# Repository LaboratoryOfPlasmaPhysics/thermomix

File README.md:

View this project on [CADLAB.io](https://cadlab.io/project/27332). 

# thermomix

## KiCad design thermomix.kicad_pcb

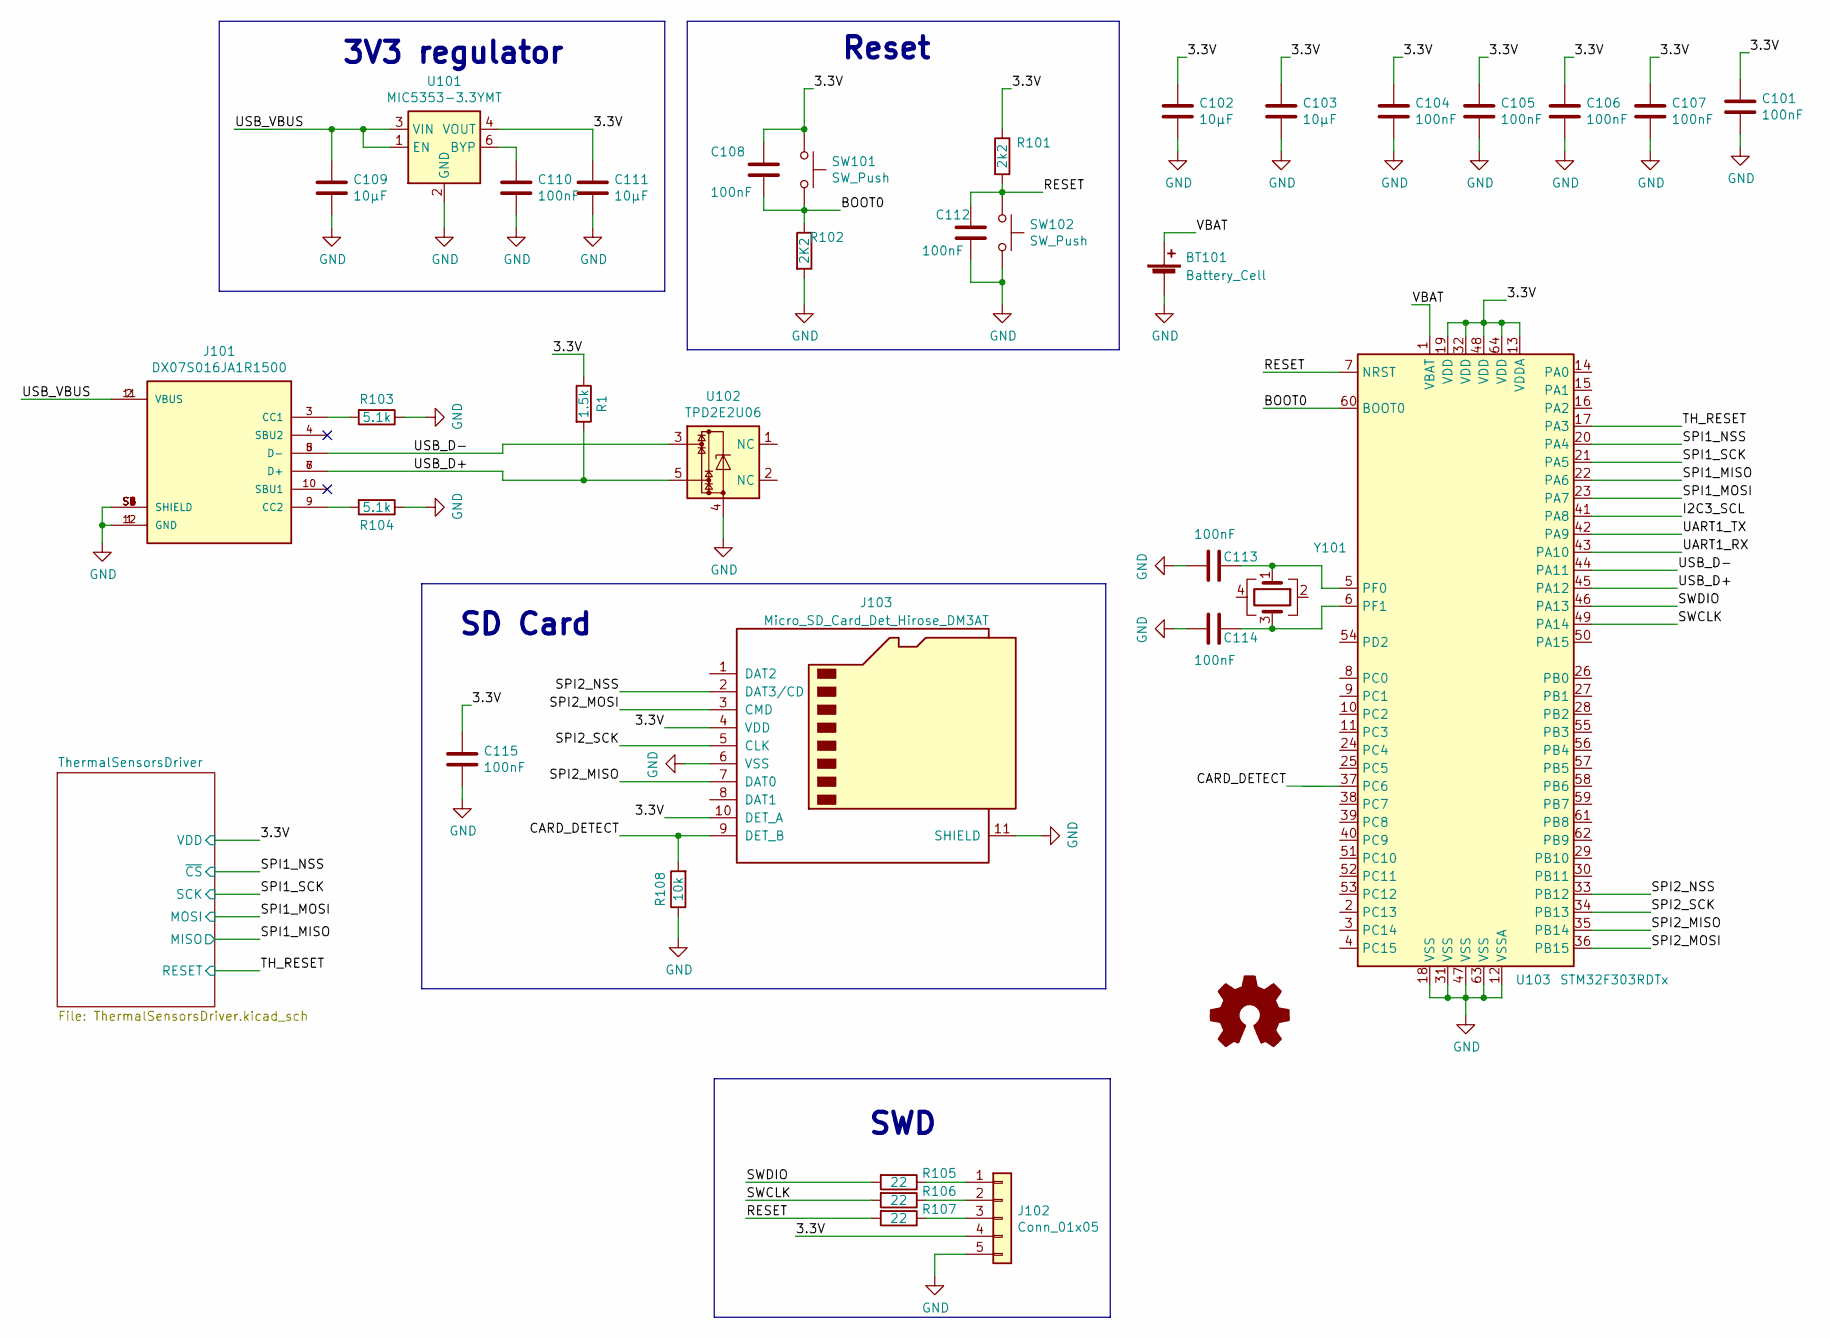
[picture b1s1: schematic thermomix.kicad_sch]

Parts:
BT101: Battery_Cell; BatteryHolder_Keystone_3000_1x12mm
C101, C104, C105, C106, C107, C108, C110, C112, C113, C114, C115: 100nF; C_0603_1608Metric_Pad1.08x0.95mm_HandSolder
C102, C103, C109, C111: 10µF; C_1206_3216Metric_Pad1.33x1.80mm_HandSolder
J101: DX07S016JA1R1500; JAE_DX07S016JA1R1500; PARTREV 1
J102: Conn_01x05; PinHeader_1x05_P2.54mm_Vertical
J103: Micro_SD_Card_Det_Hirose_DM3AT; microSD_HC_Hirose_DM3D-SF
LOGO101: Logo_Open_Hardware_Small; KiCad-Logo2_5mm_SilkScreen
R1: 1.5k; R_0603_1608Metric_Pad0.98x0.95mm_HandSolder
R101: 2k2; R_0603_1608Metric_Pad0.98x0.95mm_HandSolder
R102: 2K2; R_0603_1608Metric_Pad0.98x0.95mm_HandSolder
R103, R104: 5.1k; R_0603_1608Metric_Pad0.98x0.95mm_HandSolder
R105, R106, R107: 22; R_0603_1608Metric_Pad0.98x0.95mm_HandSolder
R108: 10k; R_0603_1608Metric_Pad0.98x0.95mm_HandSolder
SW101, SW102: SW_Push; SW_SPST_TL3342
U101: MIC5353-3.3YMT; MLF-6-1EP_1.6x1.6mm_P0.5mm_EP0.5x1.26mm
U102: TPD2E2U06; SOT-553
U103: STM32F303RDTx; LQFP-64_10x10mm_P0.5mm
Y101: Crystal_GND24; Crystal_SMD_3225-4Pin_3.2x2.5mm_HandSoldering

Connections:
/3.3V: C101.1, C102.1, C103.1, C104.1, C105.1, C106.1, C107.1, C108.1, C111.1, C115.1, J102.4, J103.4 (VDD), J103.10 (DET_A), R1.1, R101.1, SW101.1, U101.4 (VOUT), U103.13 (VDDA), U103.19 (VDD), U103.32 (VDD), U103.48 (VDD), U103.64 (VDD); also elsewhere on the board
/BOOT0: C108.2, R102.1, SW101.2, U103.60 (BOOT0)
/CARD_DETECT: J103.9 (DET_B), R108.2, U103.37 (PC6)
/I2C3_SCL: U103.41 (PA8)
/RESET: C112.1, R101.2, R107.2, SW102.1, U103.7 (NRST)
/SPI1_MISO: U103.22 (PA6); also elsewhere on the board
/SPI1_MOSI: U103.23 (PA7); also elsewhere on the board
/SPI1_NSS: U103.20 (PA4); also elsewhere on the board
/SPI1_SCK: U103.21 (PA5); also elsewhere on the board
/SPI2_MISO: J103.7 (DAT0), U103.35 (PB14)
/SPI2_MOSI: J103.3 (CMD), U103.36 (PB15)
/SPI2_NSS: J103.2 (DAT3/CD), U103.33 (PB12)
/SPI2_SCK: J103.5 (CLK), U103.34 (PB13)
/SWCLK: R106.2, U103.49 (PA14)
/SWDIO: R105.2, U103.46 (PA13)
/TH_RESET: U103.17 (PA3); also elsewhere on the board
/UART1_RX: U103.43 (PA10)
/UART1_TX: U103.42 (PA9)
/USB_D+: J101.6 (D+), J101.7 (D+), R1.2, U102.5, U103.45 (PA12)
/USB_D-: J101.5 (D-), J101.8 (D-), U102.3, U103.44 (PA11)
/USB_VBUS: C109.1, J101.2 (VBUS), J101.11 (VBUS), U101.1 (EN), U101.3 (VIN)
/VBAT: BT101.1 (+), U103.1 (VBAT)
GND: BT101.2 (-), C101.2, C102.2, C103.2, C104.2, C105.2, C106.2, C107.2, C109.2, C110.2, C111.2, C112.2, C113.1, C114.1, C115.2, J101.1 (GND), J101.12 (GND), J101.S1 (SHIELD), J101.S2 (SHIELD), J101.S3 (SHIELD), J101.S4 (SHIELD), J101.S5 (SHIELD), J101.S6 (SHIELD), J102.5, J103.6 (VSS), J103.11 (SHIELD), R102.2, R103.1, R104.1, R108.1, SW102.2, U101.2 (GND), U101.7 (GND), U102.4, U103.12 (VSSA), U103.18 (VSS), U103.31 (VSS), U103.47 (VSS), U103.63 (VSS); also elsewhere on the board
unnamed: C110.1, U101.6 (BYP)
unnamed: C113.2, U103.5 (PF0), Y101.1
unnamed: C114.2, U103.6 (PF1), Y101.3
unnamed: J101.3 (CC1), R103.2
unnamed: J101.9 (CC2), R104.2
unnamed: J102.1, R105.1
unnamed: J102.2, R106.1
unnamed: J102.3, R107.1

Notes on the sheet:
SD Card
SWD
Reset
3V3 regulator

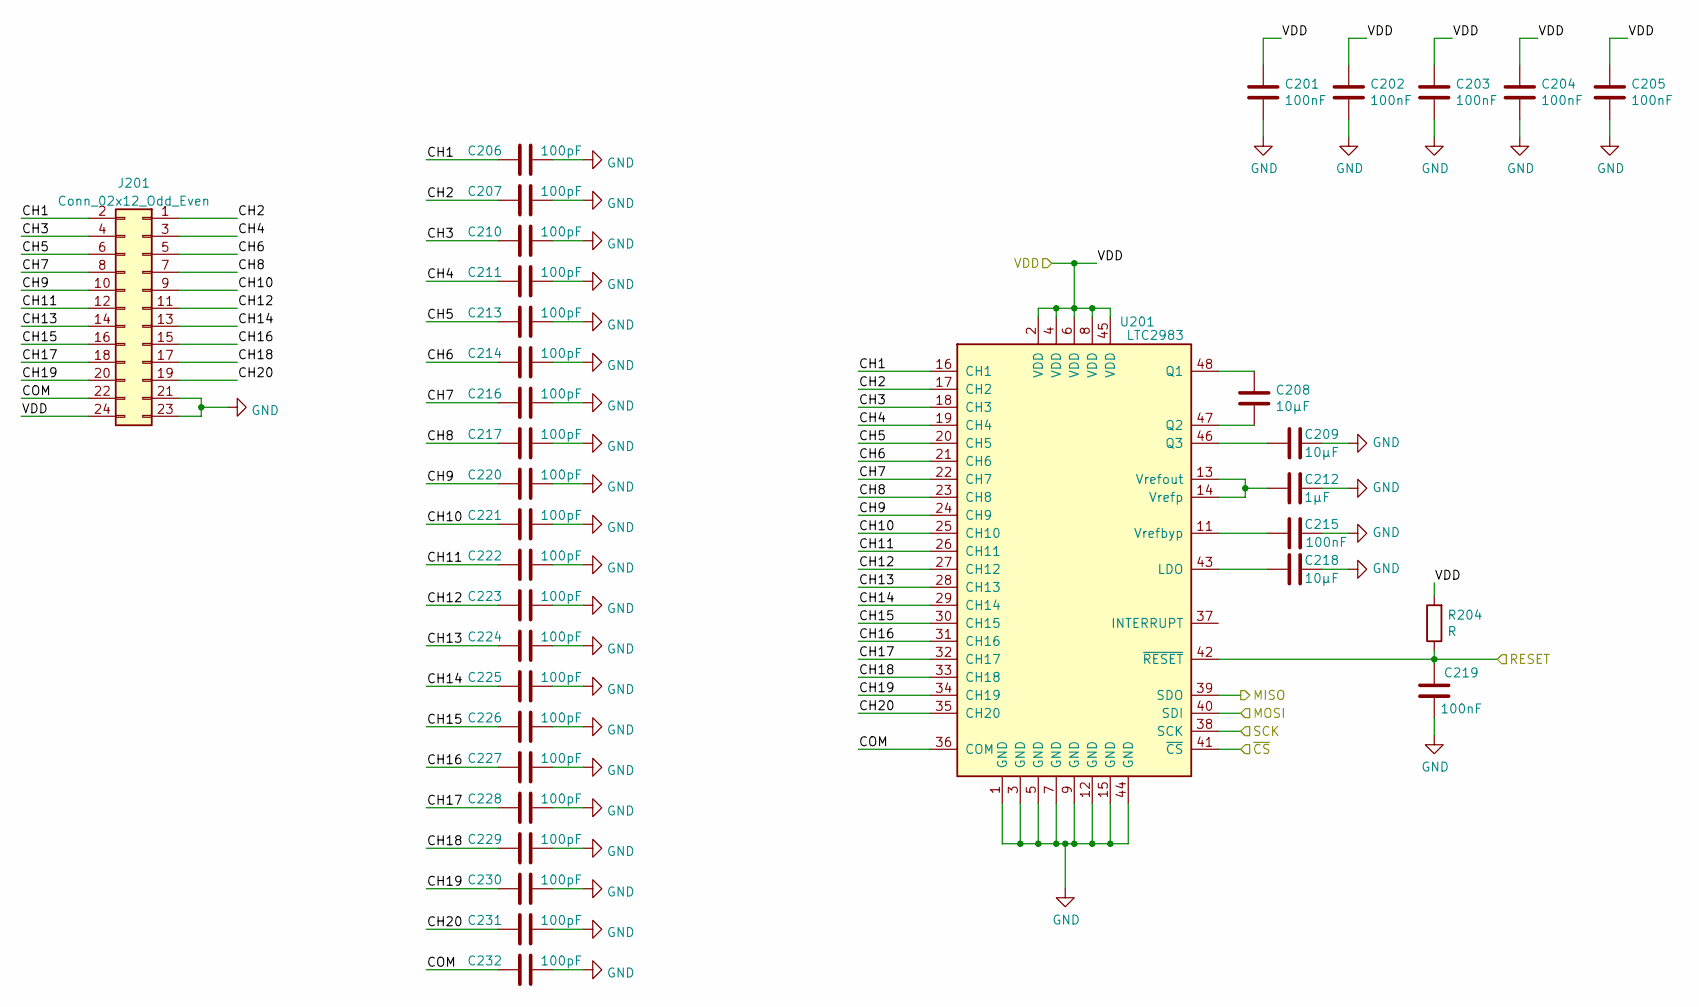
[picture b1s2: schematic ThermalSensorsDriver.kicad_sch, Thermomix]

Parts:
C201, C202, C203, C204, C205, C215, C219: 100nF; C_0603_1608Metric_Pad1.08x0.95mm_HandSolder
C206, C207, C210, C211, C213, C214, C216, C217, C220, C221, C222, C223, C224, C225, C226, C227, C228, C229, C230, C231, C232: 100pF; C_0402_1005Metric_Pad0.74x0.62mm_HandSolder
C208, C209, C218: 10µF; C_1206_3216Metric_Pad1.33x1.80mm_HandSolder
C212: 1µF; C_1206_3216Metric_Pad1.33x1.80mm_HandSolder
J201: Conn_02x12_Odd_Even; PinHeader_2x12_P2.54mm_Vertical
R204: R; R_0603_1608Metric_Pad0.98x0.95mm_HandSolder
U201: LTC2983; LQFP-48_7x7mm_P0.5mm

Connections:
/3.3V: C201.2, C202.2, C203.2, C204.2, C205.2, J201.24, R204.2, U201.2 (VDD), U201.4 (VDD), U201.6 (VDD), U201.8 (VDD), U201.45 (VDD); also elsewhere on the board
/SPI1_MISO: U201.39 (SDO); also elsewhere on the board
/SPI1_MOSI: U201.40 (SDI); also elsewhere on the board
/SPI1_NSS: U201.41 (~CS); also elsewhere on the board
/SPI1_SCK: U201.38 (SCK); also elsewhere on the board
/TH_RESET: C219.2, R204.1, U201.42 (~RESET); also elsewhere on the board
/ThermalSensorsDriver/CH1: C206.1, J201.2, U201.16 (CH1)
/ThermalSensorsDriver/CH2: C207.1, J201.1, U201.17 (CH2)
/ThermalSensorsDriver/CH3: C210.1, J201.4, U201.18 (CH3)
/ThermalSensorsDriver/CH4: C211.1, J201.3, U201.19 (CH4)
/ThermalSensorsDriver/CH5: C213.1, J201.6, U201.20 (CH5)
/ThermalSensorsDriver/CH6: C214.1, J201.5, U201.21 (CH6)
/ThermalSensorsDriver/CH7: C216.1, J201.8, U201.22 (CH7)
/ThermalSensorsDriver/CH8: C217.1, J201.7, U201.23 (CH8)
/ThermalSensorsDriver/CH9: C220.1, J201.10, U201.24 (CH9)
/ThermalSensorsDriver/CH10: C221.1, J201.9, U201.25 (CH10)
/ThermalSensorsDriver/CH11: C222.1, J201.12, U201.26 (CH11)
/ThermalSensorsDriver/CH12: C223.1, J201.11, U201.27 (CH12)
/ThermalSensorsDriver/CH13: C224.1, J201.14, U201.28 (CH13)
/ThermalSensorsDriver/CH14: C225.1, J201.13, U201.29 (CH14)
/ThermalSensorsDriver/CH15: C226.1, J201.16, U201.30 (CH15)
/ThermalSensorsDriver/CH16: C227.1, J201.15, U201.31 (CH16)
/ThermalSensorsDriver/CH17: C228.1, J201.18, U201.32 (CH17)
/ThermalSensorsDriver/CH18: C229.1, J201.17, U201.33 (CH18)
/ThermalSensorsDriver/CH19: C230.1, J201.20, U201.34 (CH19)
/ThermalSensorsDriver/CH20: C231.1, J201.19, U201.35 (CH20)
/ThermalSensorsDriver/COM: C232.1, J201.22, U201.36 (COM)
GND: C201.1, C202.1, C203.1, C204.1, C205.1, C206.2, C207.2, C209.1, C210.2, C211.2, C212.1, C213.2, C214.2, C215.1, C216.2, C217.2, C218.1, C219.1, C220.2, C221.2, C222.2, C223.2, C224.2, C225.2, C226.2, C227.2, C228.2, C229.2, C230.2, C231.2, C232.2, J201.21, J201.23, U201.1 (GND), U201.3 (GND), U201.5 (GND), U201.7 (GND), U201.9 (GND), U201.12 (GND), U201.15 (GND), U201.44 (GND); also elsewhere on the board
unnamed: C208.1, U201.47 (Q2)
unnamed: C208.2, U201.48 (Q1)
unnamed: C209.2, U201.46 (Q3)
unnamed: C212.2, U201.13 (Vrefout), U201.14 (Vrefp)
unnamed: C215.2, U201.11 (Vrefbyp)
unnamed: C218.2, U201.43 (LDO)

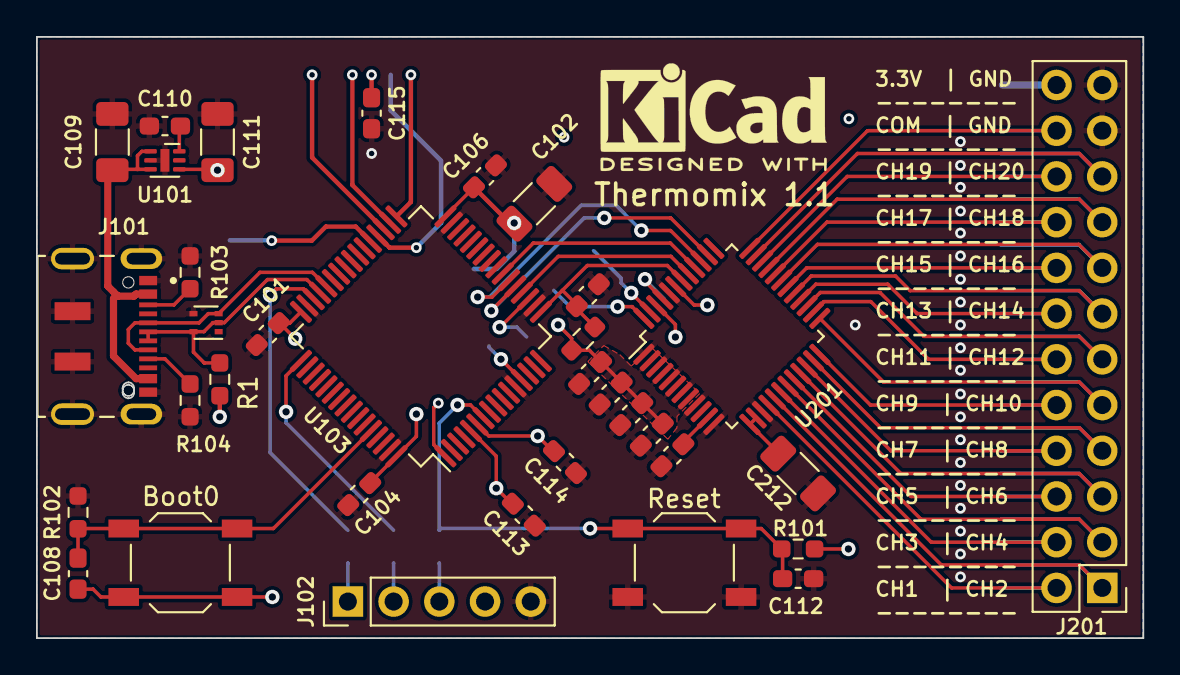
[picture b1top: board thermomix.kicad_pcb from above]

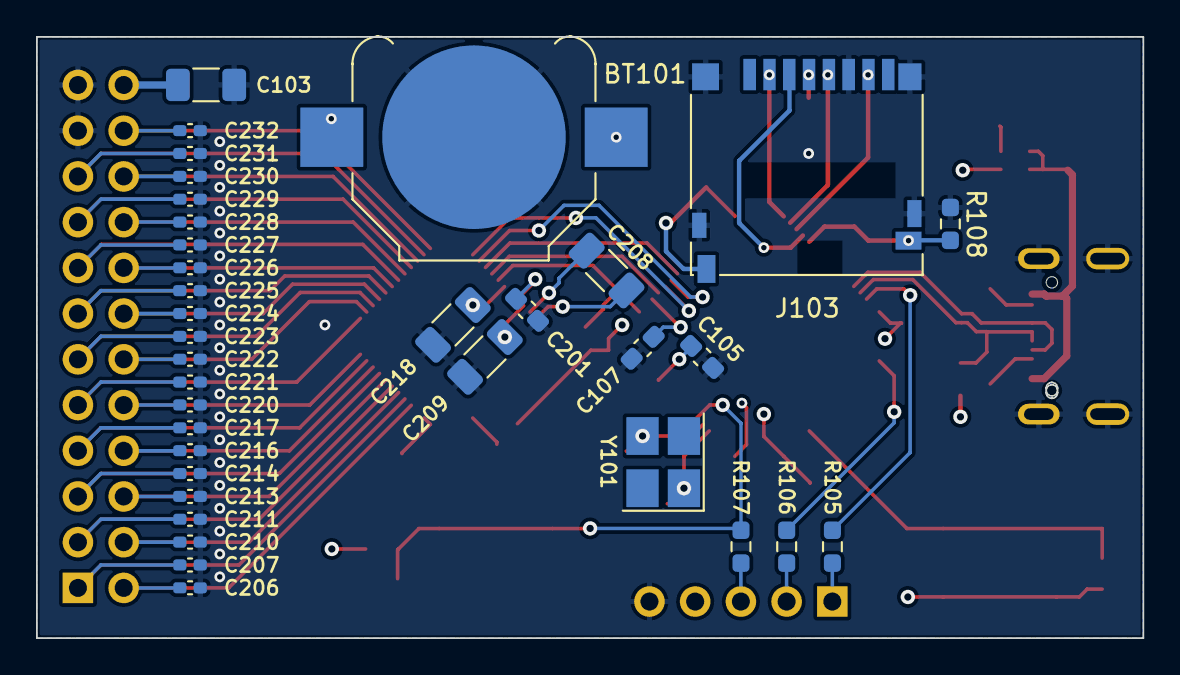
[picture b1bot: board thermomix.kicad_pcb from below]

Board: 4 copper layers, 61.5 x 33.4 mm, 70 parts (35 on the bottom side), 55 nets.

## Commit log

2022-02-28 First layout without silkscreen
2022-05-28 Silk-screen done
2022-05-30 Adds sdcard and battery
2022-06-03 1.0 release
2023-02-07 Fixes issues from revision 1.0
2023-02-07 Fixes bugs from 1.0
2023-09-13 Backlink to CADLAB.io has been added.
